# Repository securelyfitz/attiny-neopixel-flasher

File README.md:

# attiny-neopixel-flasher
quick and dirty lipo + neopixel flasher making use of parts on hand

## Circuit
Power provided by a lipo battery using a 1mm pitch 4-pin jst connector.
Power connects to the ATTINY85 and neopixels
Button connects to reset - the ATTINY keeps track of which pattern it's on in eeprom, and plays the next one at reset.

## Power saving hack
WS2182's consume 1mA when off, discharging the 1000mAh pack in a day, so now I power them with ATTINY GPIO pins. ATTINY GPIO pins provide max 40mA each 60mA combined, so I scratched off the trace and soldered a bodge wire to two pins (2+3) and the vcc pin of the neopixel ring

## PCB
Using all built-in footprints, manually placed 1x1 headers for connection to the 16-neopixel rings i have on hand. Optimized for milling with fat bits, so i removed pins 2,3,6,7 from the attiny footprint. Still need to use a V bit to get the space between the power connector pins but the rest is 1/32" flat end. Sized to match the batteries i had lying around.

## Software
Based on adafruit's neopixel strandtest with minor additions:
* use EEPROM to store/load state on reset
* choose patterns based on switch statement of eeprom state
* looped patters to each last ~60s
* use sleep.h features to go to sleep after pattern runs through
* toggle pins 3&4 to provide power for neopixels
* added rainbowall pattern to do same rainbow color to all leds
Used Arduino IDE with https://github.com/SpenceKonde/ATTinyCore for attiny85 support.

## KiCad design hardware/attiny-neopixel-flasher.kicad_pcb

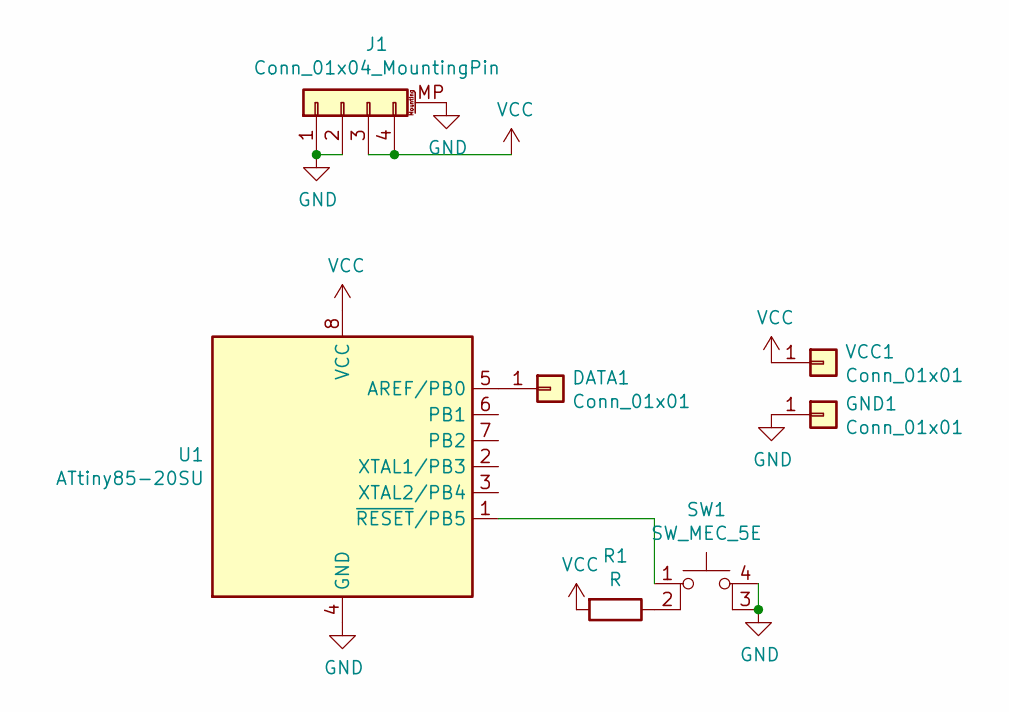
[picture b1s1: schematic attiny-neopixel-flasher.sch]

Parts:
DATA1: Conn_01x01; PinHeader_1x01_P2.54mm_Vertical
GND1: Conn_01x01; PinHeader_1x01_P2.54mm_Vertical
J1: Conn_01x04_MountingPin; JST_SH_SM04B-SRSS-TB_1x04-1MP_P1.00mm_Horizontal
R1: R; R_1206_3216Metric
SW1: SW_MEC_5E; SW_TH_Tactile_Omron_B3F-10xx
U1: ATtiny85-20SU; SOIJ-8_5.3x5.3mm_P1.27mm
VCC1: Conn_01x01; PinHeader_1x01_P2.54mm_Vertical

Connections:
GND: GND1.1, J1.1, J1.2, J1.MP (MountPin), SW1.3 (K), SW1.4 (A), U1.4 (GND)
unnamed: DATA1.1, U1.5 (AREF/PB0)
unnamed: R1.1, SW1.2
unnamed: SW1.1, U1.1 (~RESET~/PB5)
VCC: J1.3, J1.4, R1.2, U1.8 (VCC), VCC1.1

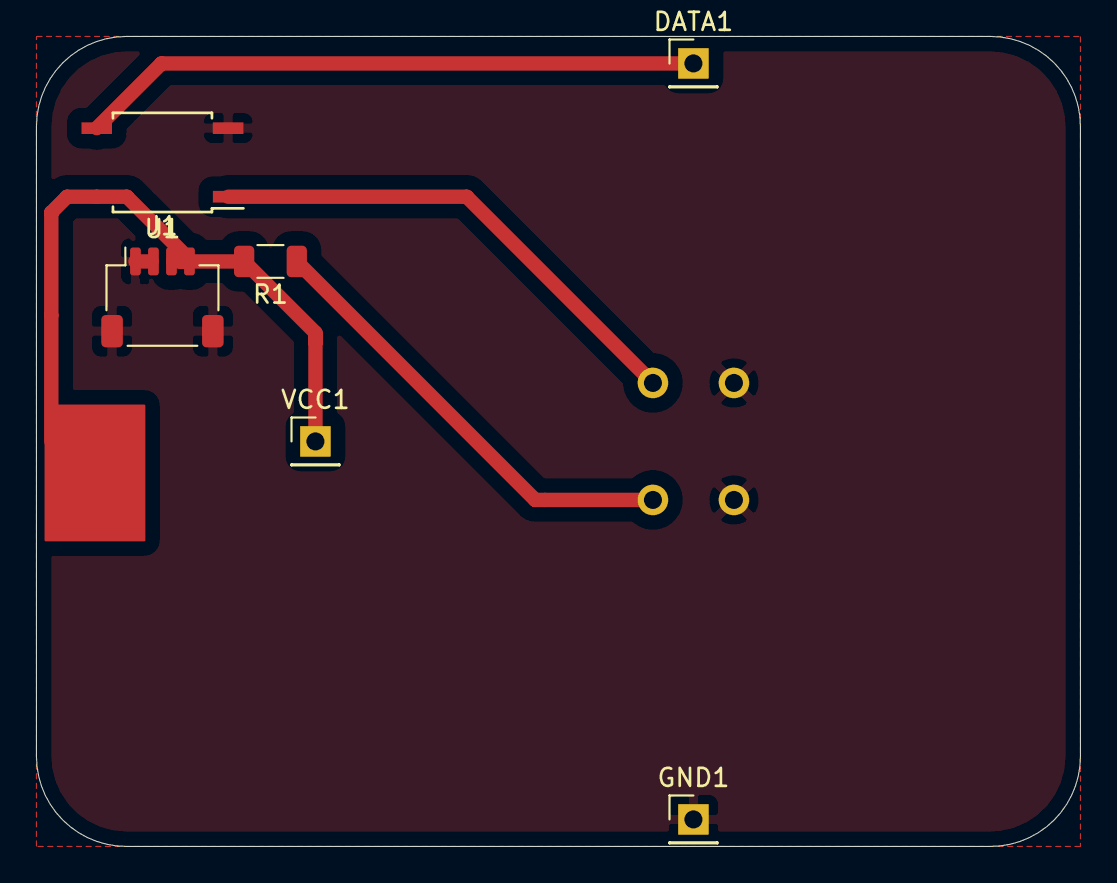
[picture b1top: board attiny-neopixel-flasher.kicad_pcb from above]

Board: 2 copper layers, 58.0 x 45.0 mm, 7 parts (1 on the bottom side), 5 nets.

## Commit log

2021-11-15 adding arduino sketch based on adafruit's strandtest
2021-11-15 adding kicad recommended gitignore
2021-11-15 adding pcb
